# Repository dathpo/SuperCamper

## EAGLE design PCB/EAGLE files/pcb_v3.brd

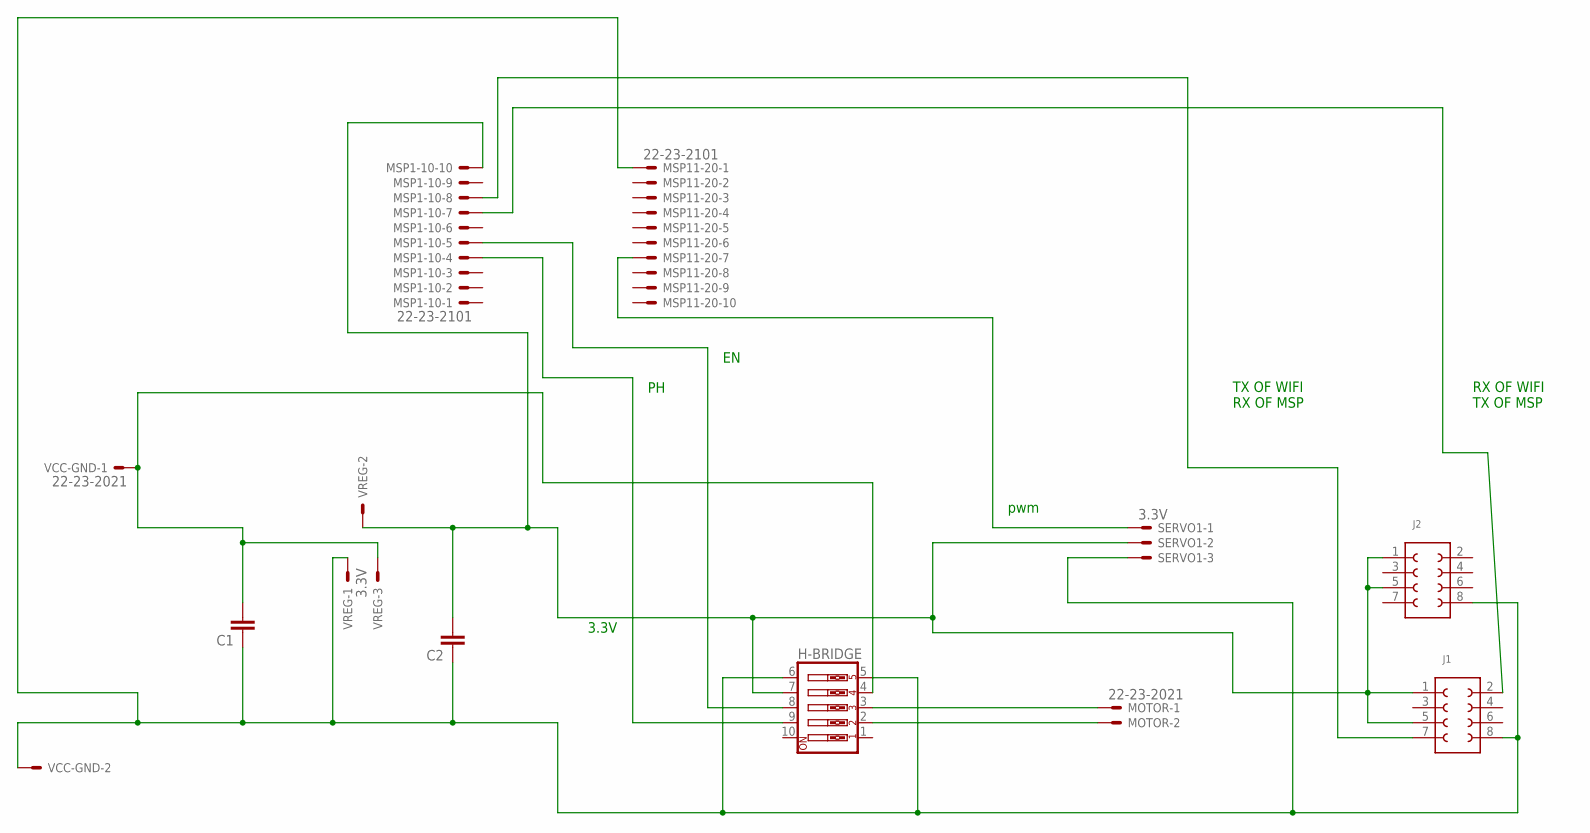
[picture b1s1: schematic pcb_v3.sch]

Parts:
C1, C2: C2,5-3; C2.5-3
H-BRIDGE: SW_DIP-5; EDG-05
J1, J2: 61300821121
MOTOR: 22-23-2021
MSP1-10, MSP11-20: 22-23-2101
SERVO1: 3.3V; 22-23-2031
VCC-GND: 22-23-2021
VREG: 3.3V; 22-23-2031

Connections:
unnamed: J1.2 (8), MSP1-10.7
unnamed: J1.7 (4), MSP1-10.8
unnamed: C2.2, H-BRIDGE.7, J1.1, J1.5 (3), J2.1, J2.5 (3), MSP1-10.10, SERVO1.2, VREG.2
unnamed: H-BRIDGE.3, MOTOR.1
unnamed: H-BRIDGE.2, MOTOR.2
unnamed: MSP11-20.7, SERVO1.1
unnamed: H-BRIDGE.8, MSP1-10.5
unnamed: C1.1, C2.1, H-BRIDGE.5, H-BRIDGE.6, J1.8 (5), J2.8 (5), MSP11-20.1, SERVO1.3, VCC-GND.2, VREG.1
unnamed: H-BRIDGE.9, MSP1-10.4
unnamed: C1.2, H-BRIDGE.4, VCC-GND.1, VREG.3

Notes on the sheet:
3.3V
pwm
TX OF WIFI RX OF MSP
RX OF WIFI TX OF MSP

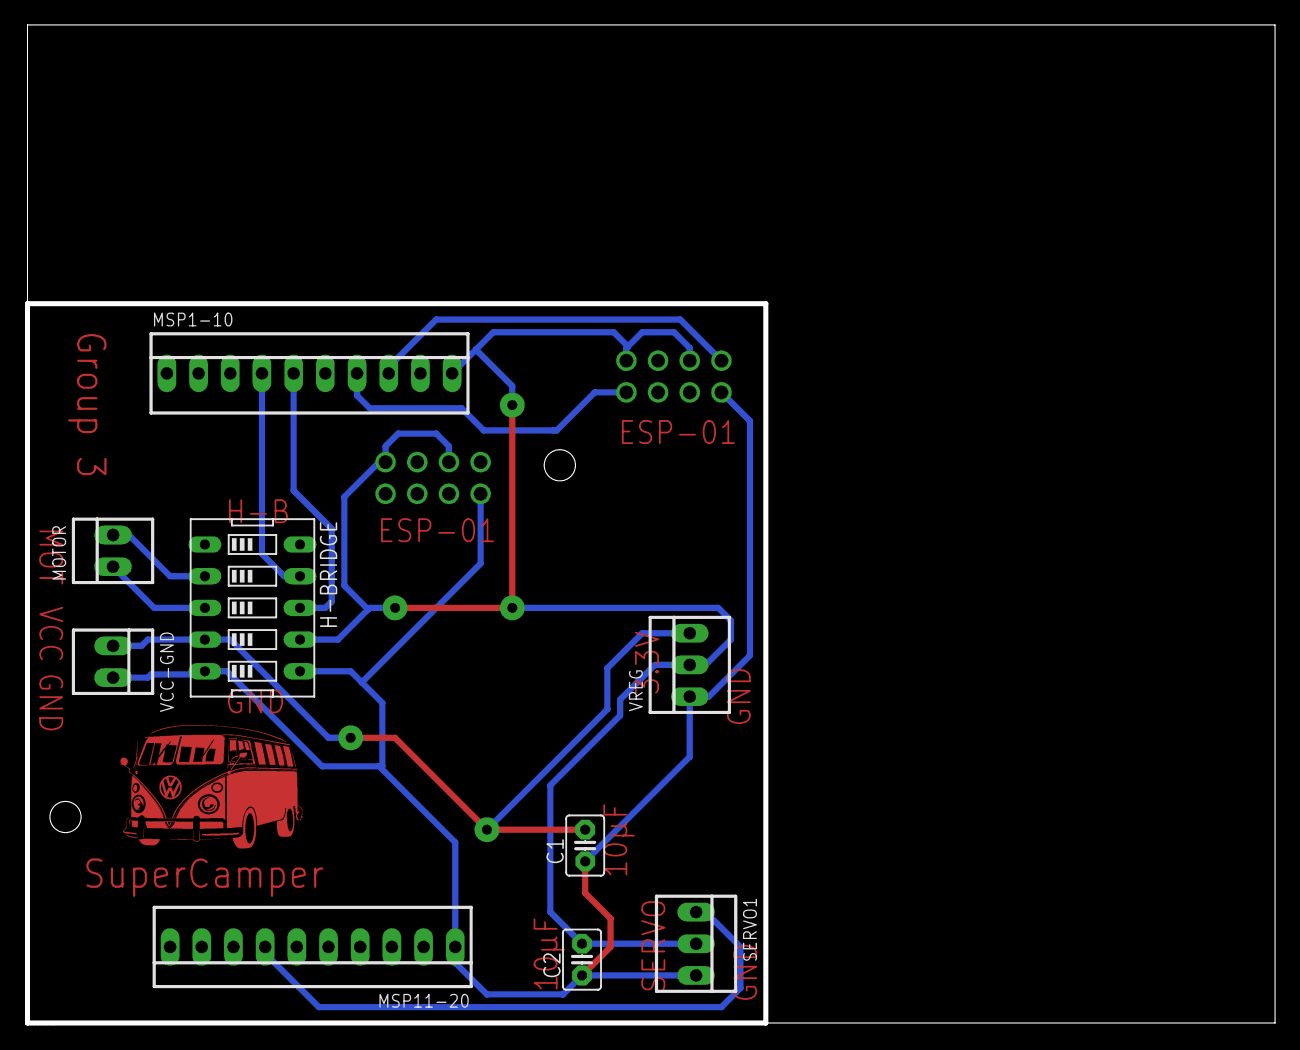
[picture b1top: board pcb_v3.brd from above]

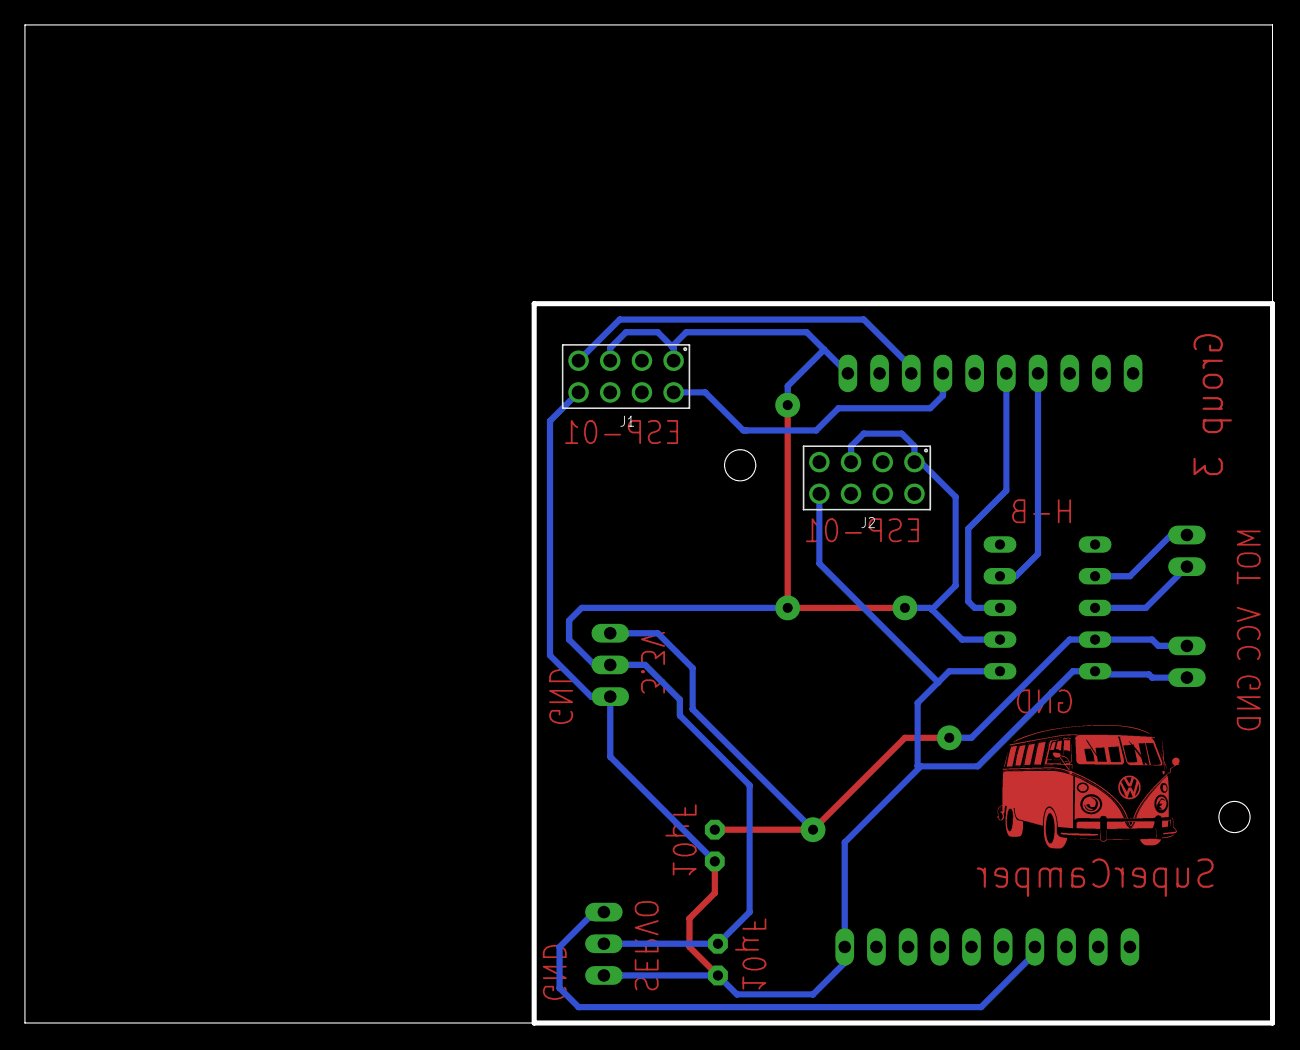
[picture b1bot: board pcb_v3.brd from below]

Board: 2 copper layers, 100.0 x 80.0 mm, 11 parts (2 on the bottom side), 10 nets.

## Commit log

2018-02-18 Update Readme with some Resources
2018-02-19 Add working Servo and WiFi C files
2018-02-19 Add AT Instruction Set, QSG for firmware update
2018-02-19 Add project that uses ESP8266 as Server and Client
2018-02-20 Add Google Docs link for notes
2018-02-20 Initial wifi chip config
2018-02-20 Left/right servo commands through Wifi module
2018-02-27 Left/right/center progress
2018-02-27 Adding app/updated gitignore
2018-02-27 App project
2018-02-28 Project clean up, app button control improvements
2018-03-01 App UI improvements
2018-03-01 Reposition buttons for 16:9 screen, implement UP/DOWN
2018-04-04 Add EAGLE PCB design files, MCU Motor Control code to be merged
2018-04-04 Include some useful files
2018-04-11 PCB v2.0 designed and ready
    + and - could be added to motor direction pins
2018-04-11 Merge motor control code with MCU main
    Motor direction still reversed by button
2018-04-20 Improvements on MSP430 WiFi setup, still WOP
2018-04-20 Improvements on MSP430 WiFi setup, still WIP
2018-04-20 PCB with new VR ready for print
2018-04-22 Addition of report document
2018-04-24 slight changes
2018-04-26 added logic to stop the engine
2018-04-26 Add second ESP8266 to PCB
2018-04-26 work on setting up the AT commands
2018-04-26 Add delay for WiFi Setup Transmission
2018-04-27 Fix app arrow commands not being sent to ESP8266
2018-04-27 removed unnecessary check from receiver interrupt. Some work on the timer but not quite there yet as the MSP only works in debug mode
2018-04-29 fixed a bug where the MSP would only work in debug mode
2018-05-01 Changed the app and MSP commands so that they are using the same values. The servos now rotate - logic and values have been changed. Some changes on the timers so that no delay_cycles() is being used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
2018-05-02 Create ServoFinal
2018-05-02 Rename ServoFinal to ServoFinal.c
2018-05-02 there are now 2 switches - one to turn on the engine and one to switch on reverse
2018-05-02 Update main.c
    Flags for on and off, no sleep
2018-05-03 ThisWorks
2018-05-03 forwards/backwards
2018-05-03 works but flags need to be checked
2018-05-03 esp8266 times out
2018-05-04 Everything working
2018-05-04 changed command for on/off engine
2018-05-04 the app now sends commands only on user interaction rather than on a loop with 100ms delay
2018-05-05 Changed letters to buttons for commands. Need to test with new batteries. Must fix forward/backwards with change in left/right/center
2018-05-05 change filename to main.c
2018-05-05 changed commands to numbers
2018-05-05 Working code, just need to fix the left recentering
2018-05-05 fixed the new line bug and changed the numeric values
2018-05-05 fixed a bug. Added new awesome sounds
2018-05-06 changed switch listener to trigger on drag as well
2018-05-06 Added AT+CIPSTO command for TCP timeout
2018-05-06 Code cleanup
2018-05-06 Added some comments, almost ready for report
2018-05-06 Added some comments, almost ready for report (fixed two comments, OCD kicking in)
2018-05-06 Fixed comments, removed repeated TA1CCTL0 setup
2018-05-06 Added a couple of comments
2018-05-08 Update main.c
    no delay cycles
2018-05-15 Fix missing curly bracket
2020-12-28 Modify .gitignore, delete sample tests and clean up project

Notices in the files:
parts and their libraries:
Board-to-Board: Copyright: Würth Elektronik
